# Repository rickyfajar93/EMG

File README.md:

# EMG

Final Semester Project

https://www.youtube.com/watch?v=Vz4RL5b69NY

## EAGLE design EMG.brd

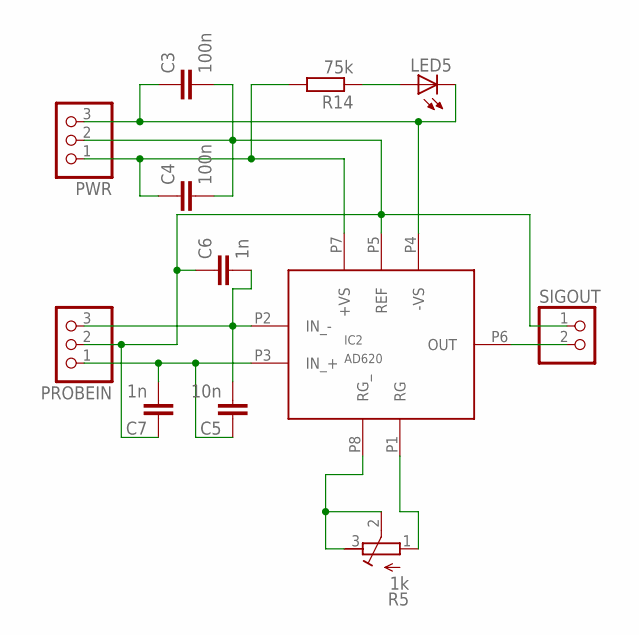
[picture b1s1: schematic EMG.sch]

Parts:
C3, C4: 100n; C050-025X075
C5: 10n; C050-025X075
C6, C7: 1n; C050-024X044
IC2: AD620; DIL8
LED5: LED3MM
PROBEIN: PINHD-1X3; 1X03
PWR: PINHD-1X3; 1X03
R5: 1k; RTRIM64X
R14: 75k; 0207/5V
SIGOUT: PINHD-1X2; 1X02

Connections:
unnamed: IC2.P8 (RG_), R5.2 (S), R5.3 (E)
unnamed: IC2.P1 (RG), R5.1 (A)
unnamed: C5.1, C7.2, IC2.P3 (IN_+), PROBEIN.1
unnamed: C5.2, C6.2, IC2.P2 (IN_-), PROBEIN.3
unnamed: C3.2, C4.2, C6.1, C7.1, IC2.P5 (REF), PROBEIN.2, PWR.2, SIGOUT.1
unnamed: C3.1, IC2.P4 (-VS), LED5.K (C), PWR.3
unnamed: C4.1, IC2.P7 (+VS), PWR.1, R14.2
unnamed: IC2.P6 (OUT), SIGOUT.2
unnamed: LED5.A, R14.1

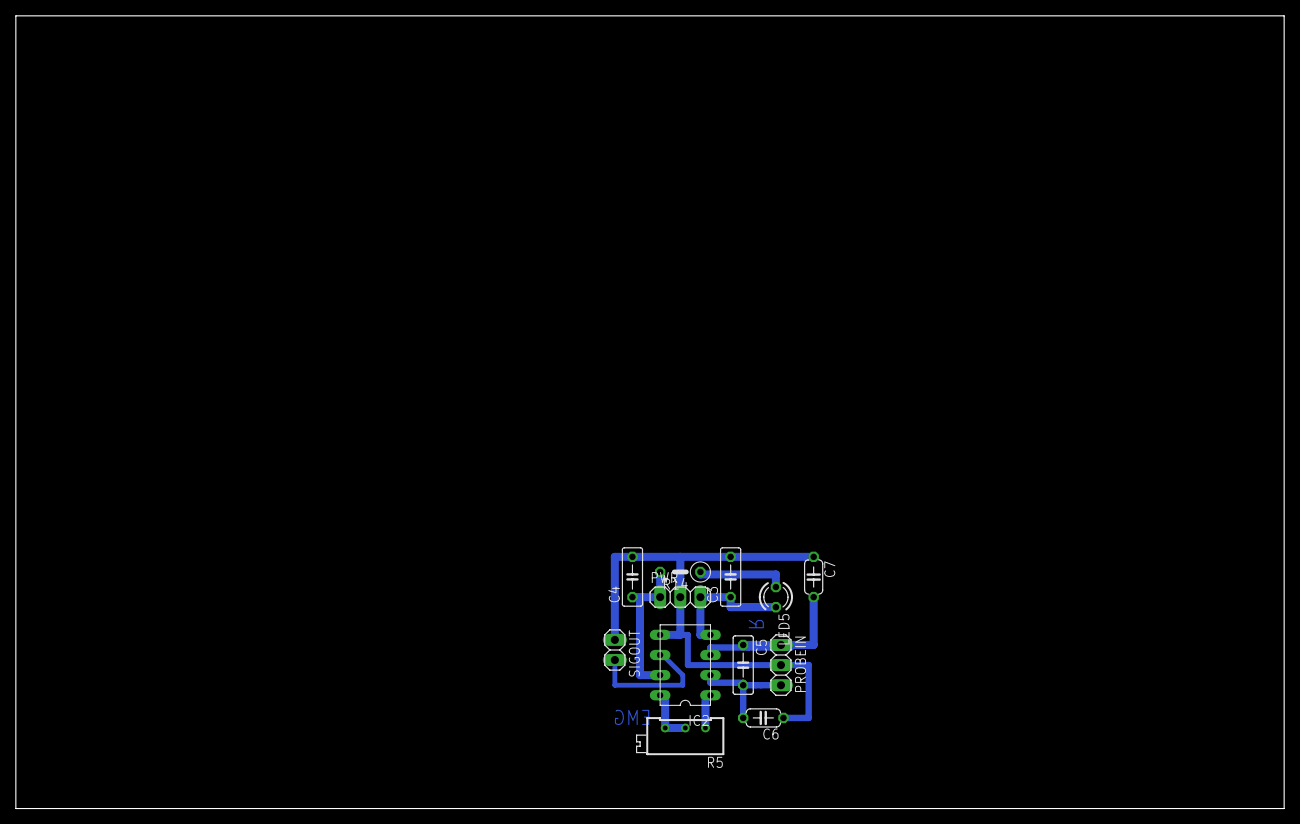
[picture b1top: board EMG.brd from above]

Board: 2 copper layers, 160.0 x 100.0 mm, 12 parts (0 on the bottom side), 9 nets.

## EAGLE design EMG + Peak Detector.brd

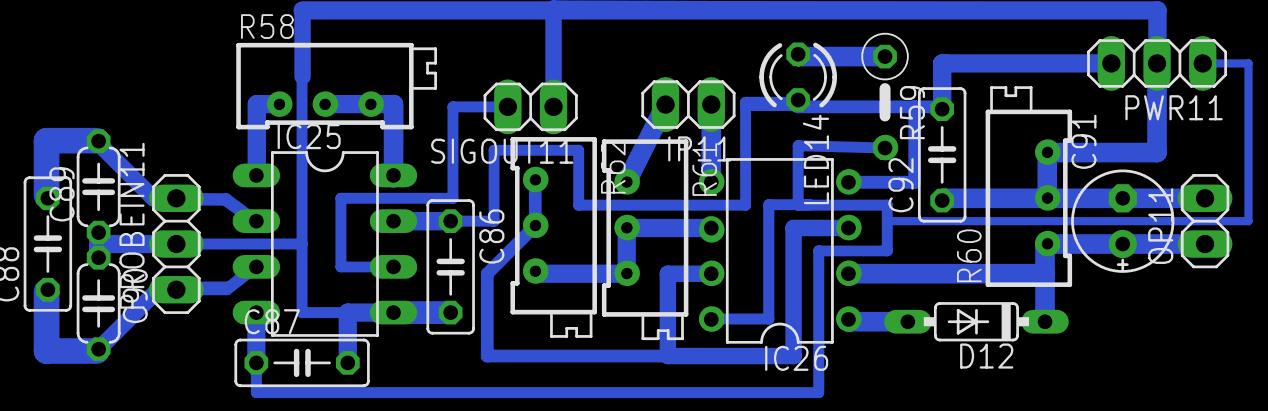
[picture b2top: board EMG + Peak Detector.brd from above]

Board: 2 copper layers, 21 parts (0 on the bottom side), 15 nets.

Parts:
C86, C87: 100n; C050-025X075
C88: 10n; C050-025X075
C89, C90: 1n; C050-024X044
C91: E2,5-6E
C92: C050-025X075
D12: 1N4148DO35-7; DO35-7
IC25: AD797N; DIL08
IC26: TL082P; DIL08
IP11: 1X02
LED14: LED3MM
OP11: 1X02
PROBEIN11: 1X03
PWR11: 1X03
R58: 200R; RTRIM64X
R59: 75k; 0207/5V
R60, R61, R62: RTRIM64X
SIGOUT11: 1X02

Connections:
unnamed: IC25.1, R58.1
unnamed: C88.1, C90.2, IC25.3, PROBEIN11.1
unnamed: C88.2, C89.2, IC25.2, PROBEIN11.3
unnamed: LED14.A, R59.1
unnamed: D12.A, IC26.1
unnamed: C86.1, C92.2, IC25.7, IC26.4, LED14.K, PWR11.3
unnamed: C87.1, IC25.4, IC26.8, PWR11.1, R59.2
unnamed: C86.2, C87.2, C89.1, C90.1, C91.-, C92.1, IC25.5, OP11.2, PROBEIN11.2, PWR11.2, R60.2, R60.3, SIGOUT11.1
unnamed: C91.+, D12.C, IC26.2, OP11.1, R60.1
unnamed: IC25.6, SIGOUT11.2
unnamed: IC26.3, IC26.7, R62.1, R62.2
unnamed: IC26.6, R61.2, R61.3, R62.3
unnamed: IP11.2, R61.1
unnamed: IC26.5, IP11.1
unnamed: IC25.8, R58.2, R58.3

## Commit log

2021-02-16 Rename Skripsi Final Single.brd to EMG + Peak Detector.brd
2021-02-16 Rename New.sch to EMG + Peak Detector.sch
